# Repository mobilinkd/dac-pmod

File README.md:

# DAC PMOD

This is a 4-channel sigma-delta DAC PMOD.  This provides an RC-filtered
and op-amp buffered output for a sigma delta modulator.

The resistor and capacitor values are not specified.  The expectation
is that users will have their own requirements for the filter cut-off.

When calculating the component values for the cut-off frequency of the
RC filter, bear in mind that a 200 ohm series resistor exists on each
PMOD signal line.

This repo contains KiCAD files and Gerbers for those wanting to make their
own boards.

This project is OSHW (Open Source Hardware), released under the GPLv3 license.

If you are interested in purchasing kits or complete modules, please contant
me at rob@mobilinkd.com.

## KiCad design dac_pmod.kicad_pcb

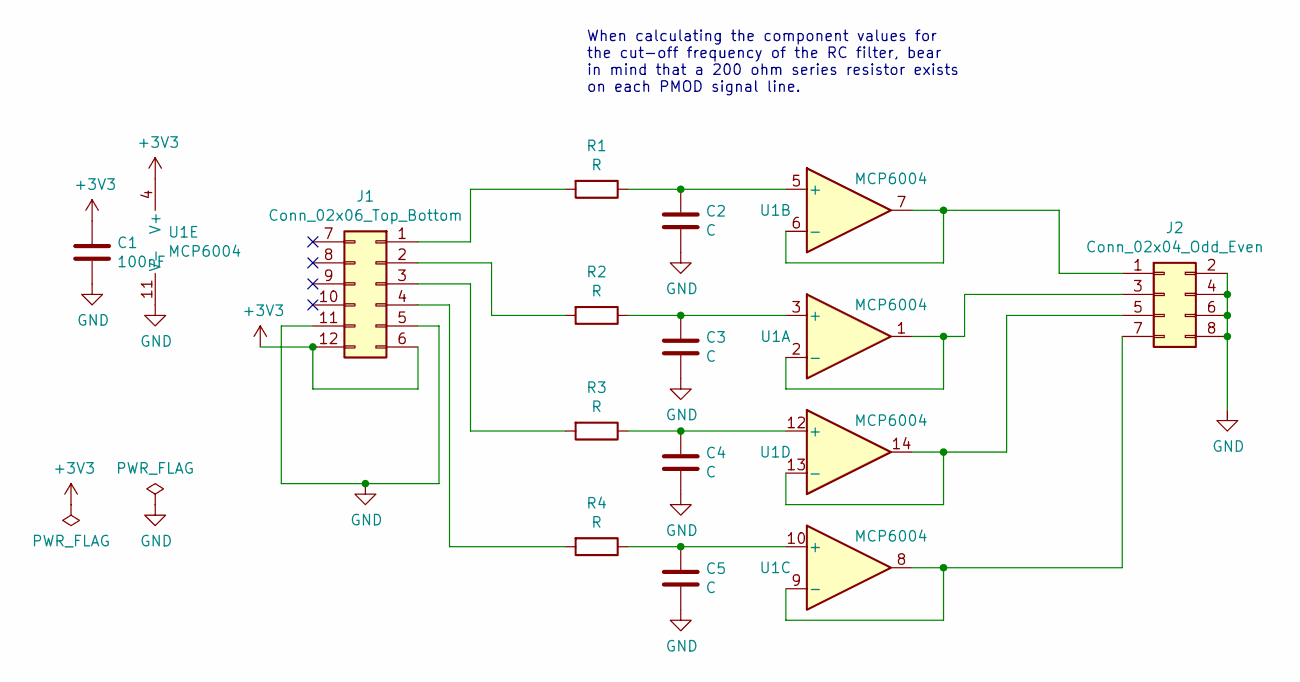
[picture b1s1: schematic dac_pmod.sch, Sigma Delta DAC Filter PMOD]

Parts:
C1: 100nF; C_0603_1608Metric_Pad1.08x0.95mm_HandSolder
C2, C3, C4, C5: C; C_0603_1608Metric_Pad1.08x0.95mm_HandSolder
J1: Conn_02x06_Top_Bottom; PinHeader_2x06_P2.54mm_Horizontal
J2: Conn_02x04_Odd_Even; PinHeader_2x04_P2.54mm_Vertical
R1, R2, R3, R4: R; R_0603_1608Metric_Pad0.98x0.95mm_HandSolder
U1: MCP6004; DIP-14_W7.62mm_Socket

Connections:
+3V3: C1.1, J1.6, J1.12, U1.4 (V+)
GND: C1.2, C2.2, C3.2, C4.2, C5.2, J1.5, J1.11, J2.2, J2.4, J2.6, J2.8, U1.11 (V-)
unnamed: C2.1, R1.1, U1.5 (+)
unnamed: C3.1, R2.1, U1.3 (+)
unnamed: C4.1, R3.1, U1.12 (+)
unnamed: C5.1, R4.1, U1.10 (+)
unnamed: J1.1, R1.2
unnamed: J1.2, R2.2
unnamed: J1.3, R3.2
unnamed: J1.4, R4.2
unnamed: J2.1, U1.6 (-), U1.7
unnamed: J2.3, U1.1, U1.2 (-)
unnamed: J2.5, U1.13 (-), U1.14
unnamed: J2.7, U1.8, U1.9 (-)

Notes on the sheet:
When calculating the component values for the cut-off frequency of the RC filter, bear in mind that a 200 ohm series resistor exists on each PMOD signal line.

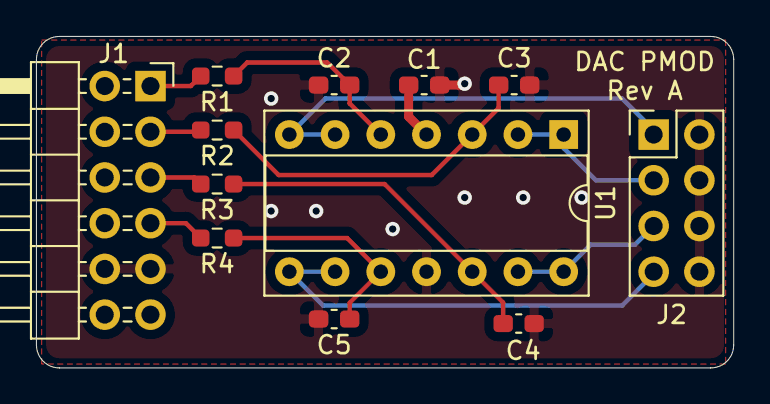
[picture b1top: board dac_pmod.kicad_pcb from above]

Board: 4 copper layers, 38.7 x 18.4 mm, 13 parts (1 on the bottom side), 14 nets.

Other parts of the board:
G1: LOGO; Mobilinkd_Logo

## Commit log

2021-10-10 Initial commit.
2021-10-21 Update to 4-layer design because... why not.
